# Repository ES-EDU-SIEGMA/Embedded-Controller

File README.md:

# Drink Mixing Machine Controller

This repository provides the source code for the RP2040 based stepper driver controller.
Further documentation of the hardware can be found in
the [main](https://git.uni-due.de/embedded-systems/student-projects/ss23-drink-mixing-machine/main) repository.

**The main branch of this repository can be considered stable and should be working at all time.**

## Local DEV Environment

### Toolchain

Required tools for the toolchain are:

- gcc (C-Compiler)
- arm-none-eabi-gcc (ARM C-Compiler)
- CMake (Build Script Generator)
- Ninja/Make (Build Tool)

### Build with CMake

#### Genrate Build Scripts

The build scripts can be generated by executing CMake in your Terminal as follows:

```bash
cmake -B build/<profile> -DUNIT_TEST:BOOL=<ON/OFF>  -DDEBUG:BOOL=<ON/OFF> -DCMAKE_BUILD_TYPE=<Debug/MinSizeRel>
```

The profile is one of three:

- _debug_
- _release_
- _unittest_

The `UNIT_TEST` option should be _ON_ for the unit-test profile and otherwise _OFF_.

The `DEBUG` option should be _OFF_ for the release profile and otherwise _ON_ to enable enhanced debug output.

The `CMAKE_BUILD_TYPE` option should be set to _MinSizeRel_ for the final targets to flash the machine for operations,
because otherwise the application provides too much output, that disturb the Python-based control application.

#### Build Targets

The targets to flash the Tiny2040 can be built by running

```bash
cmake --build build/<profile> -j4
```

The profile is one of three:

- _debug_
- _release_
- _unit-test_

## Contribution Guidelines

The source code should be formatted according to the style specified in the [.clang-format](.clang-format) file.

There are no direct commits to the main branch allowed.
If you want to contribute source-code, feel free to open a merge request with your desired changes.

### Folder Structure

The source code for the target device can be found under [src](src).
The [integration](test/integration) folder provides you with the integration tests which also double as an example for
the usage of the provided libraries.
The unit-tests aim to be executed on the local machine/server and are implemented under [unit](test/unit).

## Troubleshooting

### Serial Communication (Debugging)

The application detects the end of a send command by searching for _EOL_ (0x0A) or `\n`.
This character is not on the standard keyboard!
In minicom, for example, it can be sent with `CTRL+J`.

### Stepper Driver not working

Try with Arduino mega with example code from the TMC2209 library each stepper driver.
If the stepper driver is still not working, test after taking each of those steps:

- Check each connection
- Make sure TX and RX are correctly wired
- Use multiple different stepper drivers
- Use different USB cable to connect your computer
- Replace resistors
- Try with a different computer

If it works with the Arduino, the connections are all correct.
Try again with the pico.
If it does not work:

- Replace the pico
- Use different cable to connect your computer
- Use a different computer

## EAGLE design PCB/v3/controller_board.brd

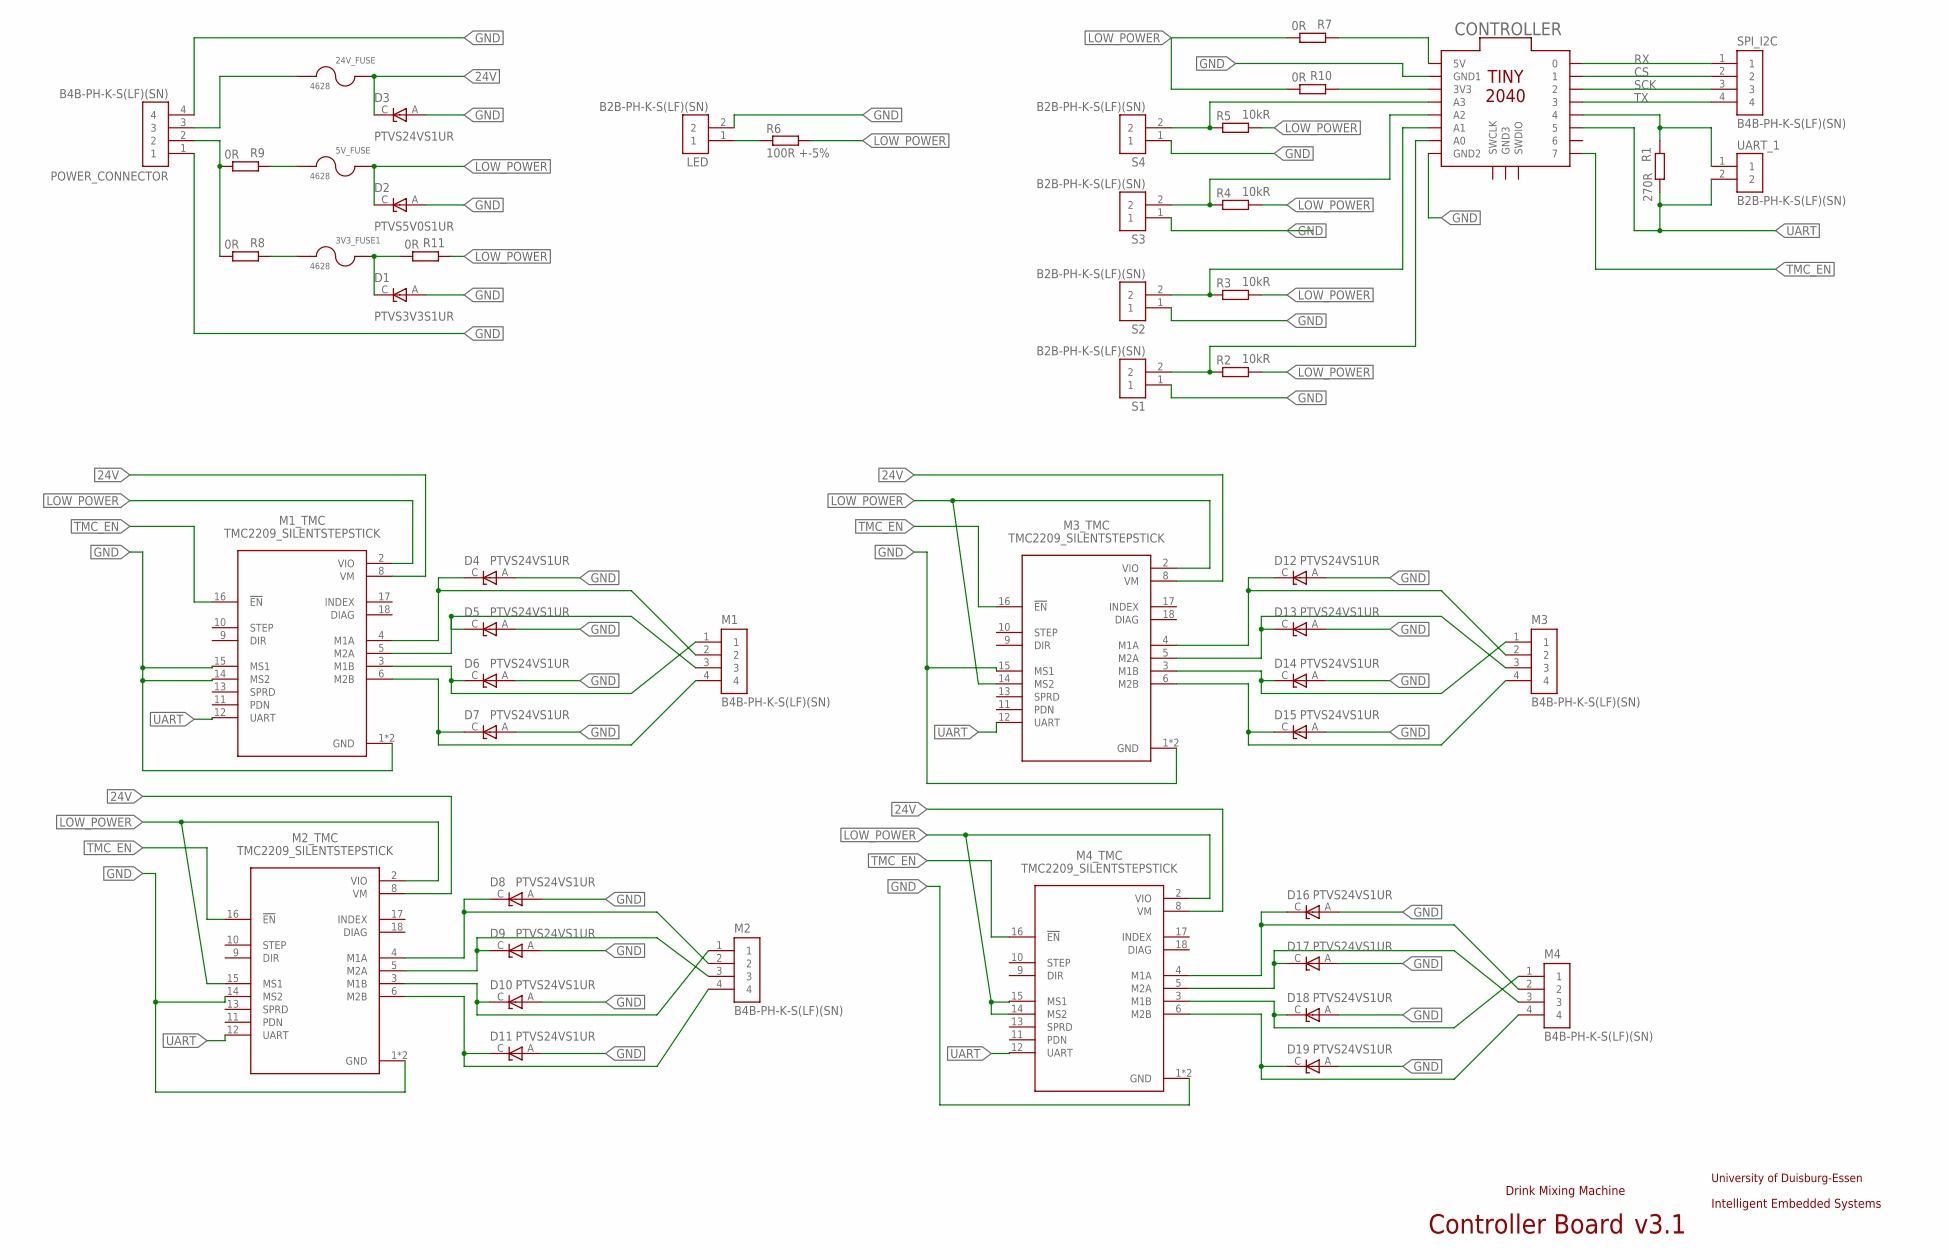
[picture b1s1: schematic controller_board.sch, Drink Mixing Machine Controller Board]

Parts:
3V3_FUSE1, 5V_FUSE, 24V_FUSE: 4628; FUSE_4628
CONTROLLER: TINY2040_HEADER
D1: PTVS3V3S1UR; TVS_PTVS3V3S1UR
D2: PTVS5V0S1UR; TVS_PTVS5V0S1UR
D3, D4, D5, D6, D7, D8, D9, D10, D11, D12, D13, D14, D15, D16, D17, D18, D19: PTVS24VS1UR; TVS_PTVS24VS1UR
LED: B2B-PH-K-S(LF)(SN); JST_B2B-PH-K-S(LF)(SN)
M1, M2, M3, M4: B4B-PH-K-S(LF)(SN); JST_B4B-PH-K-S(LF)(SN)
M1_TMC, M2_TMC, M3_TMC, M4_TMC: TMC2209_SILENTSTEPSTICK; MODULE_TMC2209_SILENTSTEPSTICK
POWER_CONNECTOR: B4B-PH-K-S(LF)(SN); JST_B4B-PH-K-S(LF)(SN)
R1: 270R; R0805
R2, R3, R4, R5: 10kR; R0805
R6: 100R +-5%; R0805
R7, R8, R9, R10, R11: 0R; R0805
S1, S2, S3, S4: B2B-PH-K-S(LF)(SN); JST_B2B-PH-K-S(LF)(SN)
SPI_I2C: B4B-PH-K-S(LF)(SN); JST_B4B-PH-K-S(LF)(SN)
UART_1: B2B-PH-K-S(LF)(SN); JST_B2B-PH-K-S(LF)(SN)

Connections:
3V3: 3V3_FUSE1.2, D1.C, R11.2
24V: 24V_FUSE.2, D3.C, M1_TMC.8 (VM), M2_TMC.8 (VM), M3_TMC.8 (VM), M4_TMC.8 (VM)
A0: CONTROLLER.A0, R2.1, S1.2
A1: CONTROLLER.A1, R3.1, S2.2
A2: CONTROLLER.A2, R4.1, S3.2
CS: CONTROLLER.1, SPI_I2C.2
GND: CONTROLLER.GND1, CONTROLLER.GND2, D1.A, D2.A, D3.A, D4.A, D5.A, D6.A, D7.A, D8.A, D9.A, D10.A, D11.A, D12.A, D13.A, D14.A, D15.A, D16.A, D17.A, D18.A, D19.A, LED.2, M1_TMC.1 (GND), M1_TMC.7 (GND), M1_TMC.14 (MS2), M1_TMC.15 (MS1), M2_TMC.1 (GND), M2_TMC.7 (GND), M2_TMC.14 (MS2), M3_TMC.1 (GND), M3_TMC.7 (GND), M3_TMC.15 (MS1), M4_TMC.1 (GND), M4_TMC.7 (GND), POWER_CONNECTOR.1, POWER_CONNECTOR.4, S1.1, S2.1, S3.1, S4.1
LOW_POWER: 5V_FUSE.2, D2.C, M1_TMC.2 (VIO), M2_TMC.2 (VIO), M2_TMC.15 (MS1), M3_TMC.2 (VIO), M3_TMC.14 (MS2), M4_TMC.2 (VIO), M4_TMC.14 (MS2), M4_TMC.15 (MS1), R2.2, R3.2, R4.2, R5.2, R6.2, R7.2, R10.2, R11.1
unnamed: POWER_CONNECTOR.2, R8.2, R9.2
unnamed: D4.C, M1.2, M1_TMC.4 (M1A)
unnamed: 5V_FUSE.1, R9.1
unnamed: D6.C, M1.1, M1_TMC.3 (M1B)
unnamed: D8.C, M2.2, M2_TMC.4 (M1A)
unnamed: D11.C, M2.4, M2_TMC.6 (M2B)
unnamed: D9.C, M2.3, M2_TMC.5 (M2A)
unnamed: D10.C, M2.1, M2_TMC.3 (M1B)
unnamed: D12.C, M3.2, M3_TMC.4 (M1A)
unnamed: D15.C, M3.4, M3_TMC.6 (M2B)
unnamed: D13.C, M3.3, M3_TMC.5 (M2A)
unnamed: D14.C, M3.1, M3_TMC.3 (M1B)
unnamed: D16.C, M4.2, M4_TMC.4 (M1A)
unnamed: D19.C, M4.4, M4_TMC.6 (M2B)
unnamed: D17.C, M4.3, M4_TMC.5 (M2A)
unnamed: D18.C, M4.1, M4_TMC.3 (M1B)
unnamed: LED.1, R6.1
unnamed: CONTROLLER.5V, R7.1
unnamed: D7.C, M1.4, M1_TMC.6 (M2B)
unnamed: CONTROLLER.4, R1.1, UART_1.1
unnamed: 3V3_FUSE1.1, R8.1
unnamed: 24V_FUSE.1, POWER_CONNECTOR.3
unnamed: CONTROLLER.3V3, R10.1
unnamed: CONTROLLER.A3, R5.1, S4.2
unnamed: D5.C, M1.3, M1_TMC.5 (M2A)
RX: CONTROLLER.0, SPI_I2C.1
SCK: CONTROLLER.2, SPI_I2C.3
TMC_EN: CONTROLLER.7, M1_TMC.16 (!EN), M2_TMC.16 (!EN), M3_TMC.16 (!EN), M4_TMC.16 (!EN)
TX: CONTROLLER.3, SPI_I2C.4
UART: CONTROLLER.5, M1_TMC.12 (UART), M2_TMC.12 (UART), M3_TMC.12 (UART), M4_TMC.12 (UART), R1.2, UART_1.2

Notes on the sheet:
Intelligent Embedded Systems
University of Duisburg-Essen
Drink Mixing Machine
Controller Board

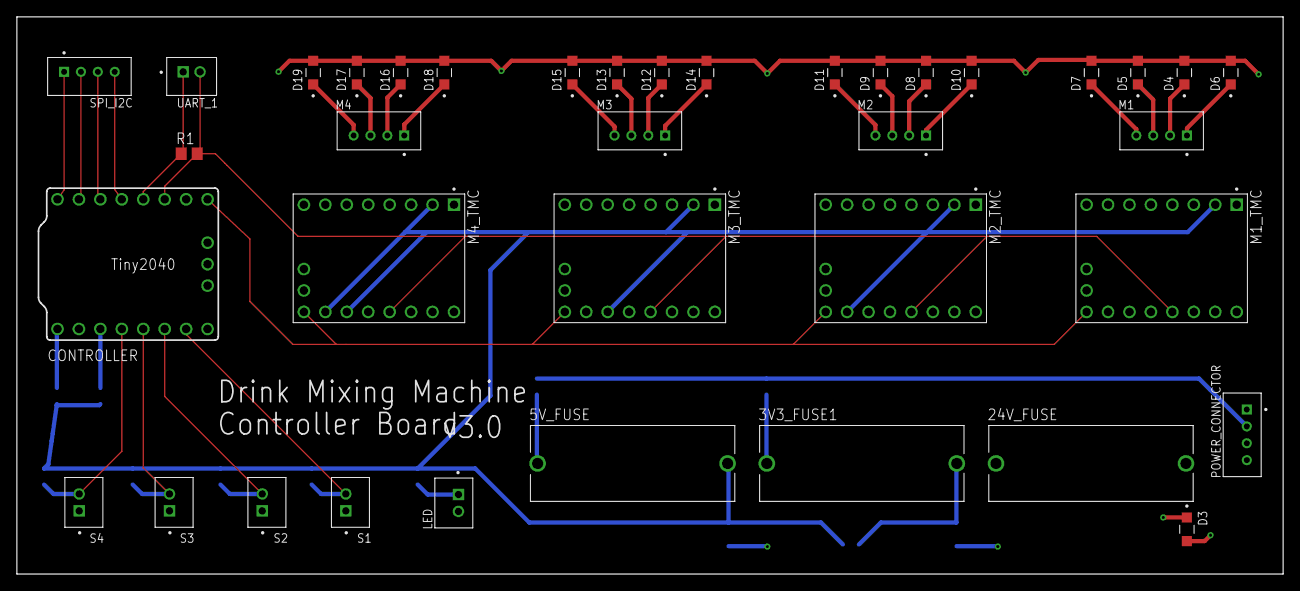
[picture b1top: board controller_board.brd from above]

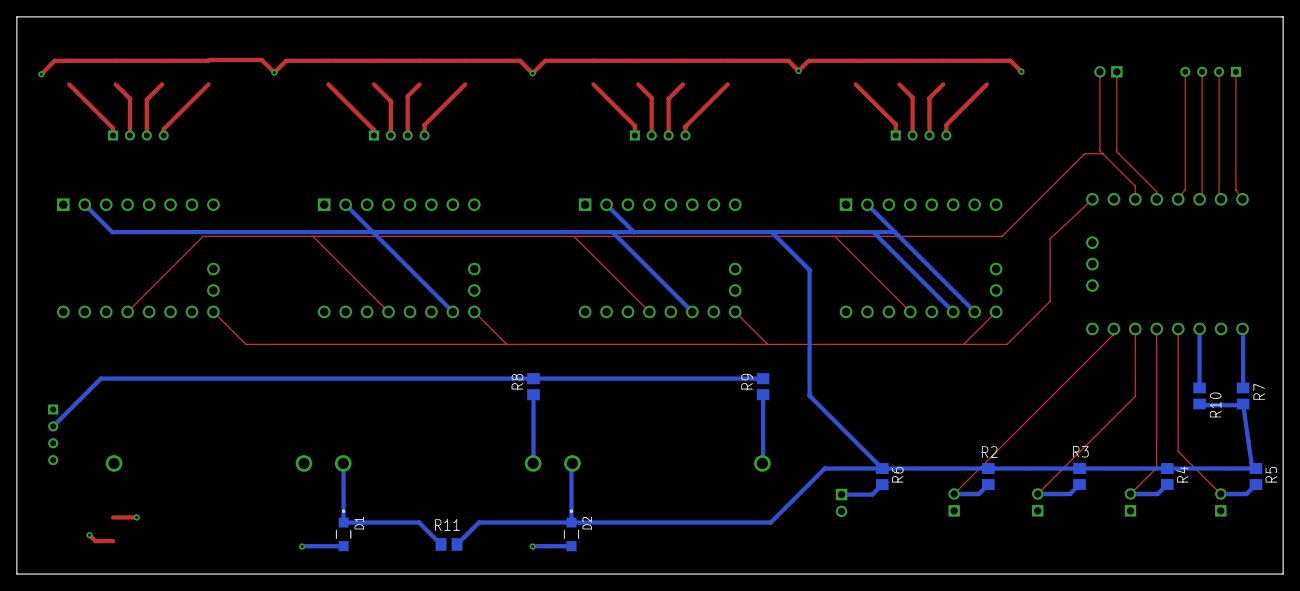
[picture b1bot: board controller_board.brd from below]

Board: 4 copper layers, 150.0 x 66.0 mm, 50 parts (12 on the bottom side), 38 nets.

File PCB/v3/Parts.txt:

Partlist

Exported from controller_board.sch at 06.02.24 19:13

EAGLE Version 9.6.2 Copyright (c) 1988-2020 Autodesk, Inc.

Assembly variant: 

Part            Value                   Device                  Package                        Library                 Sheet

3V3_FUSE1       4628                    4628                    FUSE_4628                      4628                    1
5V_FUSE         4628                    4628                    FUSE_4628                      4628                    1
24V_FUSE        4628                    4628                    FUSE_4628                      4628                    1
CONTROLLER      TINY2040_HEADER         TINY2040_HEADER         TINY2040_HEADER                tiny2040_headerd        1
D1              PTVS3V3S1UR             PTVS3V3S1UR             TVS_PTVS3V3S1UR                PTVS3V3S1UR             1
D2              PTVS5V0S1UR             PTVS5V0S1UR             TVS_PTVS5V0S1UR                PTVS5V0S1UR             1
D3              PTVS24VS1UR             PTVS24VS1UR             TVS_PTVS24VS1UR                PTVS24VS1UR             1
D4              PTVS24VS1UR             PTVS24VS1UR             TVS_PTVS24VS1UR                PTVS24VS1UR             1
D5              PTVS24VS1UR             PTVS24VS1UR             TVS_PTVS24VS1UR                PTVS24VS1UR             1
D6              PTVS24VS1UR             PTVS24VS1UR             TVS_PTVS24VS1UR                PTVS24VS1UR             1
D7              PTVS24VS1UR             PTVS24VS1UR             TVS_PTVS24VS1UR                PTVS24VS1UR             1
D8              PTVS24VS1UR             PTVS24VS1UR             TVS_PTVS24VS1UR                PTVS24VS1UR             1
D9              PTVS24VS1UR             PTVS24VS1UR             TVS_PTVS24VS1UR                PTVS24VS1UR             1
D10             PTVS24VS1UR             PTVS24VS1UR             TVS_PTVS24VS1UR                PTVS24VS1UR             1
D11             PTVS24VS1UR             PTVS24VS1UR             TVS_PTVS24VS1UR                PTVS24VS1UR             1
D12             PTVS24VS1UR             PTVS24VS1UR             TVS_PTVS24VS1UR                PTVS24VS1UR             1
D13             PTVS24VS1UR             PTVS24VS1UR             TVS_PTVS24VS1UR                PTVS24VS1UR             1
D14             PTVS24VS1UR             PTVS24VS1UR             TVS_PTVS24VS1UR                PTVS24VS1UR             1
D15             PTVS24VS1UR             PTVS24VS1UR             TVS_PTVS24VS1UR                PTVS24VS1UR             1
D16             PTVS24VS1UR             PTVS24VS1UR             TVS_PTVS24VS1UR                PTVS24VS1UR             1
D17             PTVS24VS1UR             PTVS24VS1UR             TVS_PTVS24VS1UR                PTVS24VS1UR             1
D18             PTVS24VS1UR             PTVS24VS1UR             TVS_PTVS24VS1UR                PTVS24VS1UR             1
D19             PTVS24VS1UR             PTVS24VS1UR             TVS_PTVS24VS1UR                PTVS24VS1UR             1
LED             B2B-PH-K-S(LF)(SN)      B2B-PH-K-S(LF)(SN)      JST_B2B-PH-K-S(LF)(SN)         B2B-PH-K-S_LF__SN_      1
M1              B4B-PH-K-S(LF)(SN)      B4B-PH-K-S(LF)(SN)      JST_B4B-PH-K-S(LF)(SN)         B4B-PH-K-S_LF__SN_      1
M1_TMC          TMC2209_SILENTSTEPSTICK TMC2209_SILENTSTEPSTICK MODULE_TMC2209_SILENTSTEPSTICK TMC2209_SILENTSTEPSTICK 1
M2              B4B-PH-K-S(LF)(SN)      B4B-PH-K-S(LF)(SN)      JST_B4B-PH-K-S(LF)(SN)         B4B-PH-K-S_LF__SN_      1
M2_TMC          TMC2209_SILENTSTEPSTICK TMC2209_SILENTSTEPSTICK MODULE_TMC2209_SILENTSTEPSTICK TMC2209_SILENTSTEPSTICK 1
M3              B4B-PH-K-S(LF)(SN)      B4B-PH-K-S(LF)(SN)      JST_B4B-PH-K-S(LF)(SN)         B4B-PH-K-S_LF__SN_      1
M3_TMC          TMC2209_SILENTSTEPSTICK TMC2209_SILENTSTEPSTICK MODULE_TMC2209_SILENTSTEPSTICK TMC2209_SILENTSTEPSTICK 1
M4              B4B-PH-K-S(LF)(SN)      B4B-PH-K-S(LF)(SN)      JST_B4B-PH-K-S(LF)(SN)         B4B-PH-K-S_LF__SN_      1
M4_TMC          TMC2209_SILENTSTEPSTICK TMC2209_SILENTSTEPSTICK MODULE_TMC2209_SILENTSTEPSTICK TMC2209_SILENTSTEPSTICK 1
POWER_CONNECTOR B4B-PH-K-S(LF)(SN)      B4B-PH-K-S(LF)(SN)      JST_B4B-PH-K-S(LF)(SN)         B4B-PH-K-S_LF__SN_      1
R1              270R                    R-EU_R0805              R0805                          rcl                     1
R2              10kR                    R-EU_R0805              R0805                          rcl                     1
R3              10kR                    R-EU_R0805              R0805                          rcl                     1
R4              10kR                    R-EU_R0805              R0805                          rcl                     1
R5              10kR                    R-EU_R0805              R0805                          rcl                     1
R6              100R +-5%               R-EU_R0805              R0805                          rcl                     1
R7              0R                      R-EU_R0805              R0805                          rcl                     1
R8              0R                      R-EU_R0805              R0805                          rcl                     1
R9              0R                      R-EU_R0805              R0805                          rcl                     1
R10             0R                      R-EU_R0805              R0805                          rcl                     1
R11             0R                      R-EU_R0805              R0805                          rcl                     1
S1              B2B-PH-K-S(LF)(SN)      B2B-PH-K-S(LF)(SN)      JST_B2B-PH-K-S(LF)(SN)         B2B-PH-K-S_LF__SN_      1
S2              B2B-PH-K-S(LF)(SN)      B2B-PH-K-S(LF)(SN)      JST_B2B-PH-K-S(LF)(SN)         B2B-PH-K-S_LF__SN_      1
S3              B2B-PH-K-S(LF)(SN)      B2B-PH-K-S(LF)(SN)      JST_B2B-PH-K-S(LF)(SN)         B2B-PH-K-S_LF__SN_      1
S4              B2B-PH-K-S(LF)(SN)      B2B-PH-K-S(LF)(SN)      JST_B2B-PH-K-S(LF)(SN)         B2B-PH-K-S_LF__SN_      1
SPI_I2C         B4B-PH-K-S(LF)(SN)      B4B-PH-K-S(LF)(SN)      JST_B4B-PH-K-S(LF)(SN)         B4B-PH-K-S_LF__SN_      1
UART_1          B2B-PH-K-S(LF)(SN)      B2B-PH-K-S(LF)(SN)      JST_B2B-PH-K-S(LF)(SN)         B2B-PH-K-S_LF__SN_      1

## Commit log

2023-04-19 chore(ide): remove IDE settings
2023-04-19 fix build: fixed build files / includes
2023-04-19 refactor(integration-test): apply format options
2023-04-19 refactor(unit-test): apply format
2023-04-19 docs(readme): update
2023-04-21 build(target):
    Update CMake files for target Tiny2040
2023-04-21 refactor(main):
    refactored main file for improved readability
2023-04-21 refactor(dispenser):
    refacor dispenser library for improved readability
2023-04-21 refactor(dispenser):
    refactor dispenser library for improved readability
2023-04-21 refactor(limitSwitch):
    refactor limitSwitch library for improved readability
2023-04-21 refactor(motor):
    refactor motor library for improved readability
2023-04-22 refactor(rondell):
    refactor rondell library for improved readability
2023-04-22 refactor(serialUart):
    refactor serial UART library for improved readability
2023-04-22 refactor(tmc2209):
    refactor tmc2209 library for improved readability
2023-04-22 refactor(integration-test):
    applied refactoring
2023-04-22 fix(integration-test): fix dispenser
2023-04-24 Correct mistake
2023-04-26 chore(common): add PRINT_COMMAND makro
    Add special makro for commands required for the implementation and communication with the Pi
2023-04-26 style(debug-print): apply print makros
2023-04-26 style(rondell): move static functions to internal header
2023-04-26 test(dispenser): added documentation for integration-test
2023-04-27 fix(main)(fix dispensing liquids):
    Functions was wrong due to flase refactoring
2023-04-28 fix(dispenser): change `elifdef` to `if defined(...)``
2023-04-28 fix(dispenser): replaced PRINT with PRINT_DEBUG
2023-04-28 fix(rondell): renamed RONDELL_POSITION
2023-05-09 perf(main): add watchdog timer
    add watchdog time of 15s
    improved readability by extracting code into functions
    declared function prototypes for internal functions
2023-05-09 fix(main): fix processMessage
2023-05-12 chore(git): update ignore
2023-05-12 style(main): minor changes on main loop
2023-05-14 build(target): split into three targets
    removed one main.c target and split up into left/right/rondell
    BREAKING CHANGE: Split hardware target into differnt build targets
2023-05-14 refactor(dispenser): remove LEFT/RIGHT/RONDELL flag from dispenser lib
2023-05-14 refactor(limitSwitch): update dependencies
2023-05-14 refactor(motor): update dependencies
2023-05-15 build(target): fully removed LEFT/RIGHT/RONDELL flag
2023-05-15 test(integration-test): refacor tests to compile after build script changes
2023-05-17 perf(helper): introduced helper to
    BREAKING CHANGE: description new awaits pointer to store data
2023-05-23 fix(watchdog): fix implementation so that watchdog is working correctly
2023-06-04 test(dispenser rigth side): Changed speed to 150000 and adjusted Steps. Added missing breaks.
2023-06-11 feat(speed of dispenser): New function to calculate the moving up time of the dispenser
2023-06-13 fix(rondell): add second watchdog timer reset
2023-06-18 feat(speed of dispenser): Apply Davids Code suggestions
2023-06-19 feat(speed of dispenser): Making Speed Function static
2023-06-20 Apply suggestions from code review
2023-06-27 fix(Dispenser): UpTime in Milliseconds
2023-06-27 feat(ramp for Dispenser): Two speeds are possible for the up-driving, slow and fast
2023-06-29 fix(Dispenser-Speed): Calculation of stepsPerSecond
2023-07-04 feat(dispenser): Parameter changes for ramp for Dispenser
2023-07-05 chore(git):
2023-07-05 build(pico-sdk): update pico-sdk to latest release
2023-07-05 test(dispenser): fix integration for dispeneser
2023-07-05 fix(rondell): reduce motor speed of rondell
    required due to the fact,
    that the sensor is not fast enough otherwise
2023-07-05 docs(readme): add 'how to use CMake' part
2023-07-06 feat(dispenser): If only one speed is required, set stepsFastSpeed = 0
2023-07-06 refactor(dispenser): Deleted unused variables
2023-07-07 refactor(ramp): Some Code changes and comments for a better understanding
2023-07-07 feat(torqueRecognition): Added functions to tmc2209.c
2023-07-07 feat(torqueRecognition): Torque Measuring does work
2023-07-09 feat(Dispenser): top State Detection
2023-07-10 fix(Speed of Dispenser): Adjust speed of Dispenser
2023-07-25 feat(Dispenser): Better top State Detection and downstate only reached by limitSwitch
2023-10-24 chore(PCB): moved old files to subfolder
2023-10-24 doc(PCB): add new board schematics (AUTODESK EAGLE)
2023-11-05 chore(pcb): improve schematics
2023-11-06 feat(pcb): add ESD protection
2023-11-07 refactor(Dispenser): Deleted Functions for time calculation for the up driving
2023-11-07 feat(pcb): add proper PCB layout
2023-11-07 Measuring torque - Logic of processMessage, time consumption optimized
2023-11-07 Measuring torque - Logic of processMessage, time consumption optimized. Removed testing code
2023-11-07 refactor(Dispenser): Deleted Function for direction search
2023-11-07 refactor(Dispenser): When limit switch is closed in initialization, motor does not move
2023-11-07 refactor(Dispenser): Deleted find direction function
2023-11-08 feat(pcb): add wires
2023-11-13 feat(pcb): add 3V3 circuit
2023-11-14 feat(pcb): replace ESD protection with TVS-Diode
2023-11-16 #41 perf(torque) measure torque's value more frequently.
2023-11-16 feat(pcb): add TMC enable pin
2023-11-16 chore(pcb): rename folder to correct version
2023-11-17 fix(pcb): fix tiny2040 library
2023-11-17 chore(pcb): add libraries
2023-12-01 refactoring libraries
2023-12-12 docs(pcb): added gerber files for JCLPCB 4-layer
    Added Eagle generated gerber files based on jclpcb provided CAM file
    -> added too!
2023-12-12 feat(Dispenser): The lever from all dispensers drives in the initialization directly under the dispenser and stops
2023-12-14 feat(Dispenser): The lever from all dispensers, after emptying has taken place, drives under the dispenser and stops
2023-12-14 fix(Controller): The new timing behavior for the right dipsensor and the rondel has been updated like it is in the left dispenser.
2023-12-15 feat(Dispenser): Code does work with one or two dispenser triggered, but not with 3 or more triggered
2023-12-16 refactor(dispenser): new implementation of time to hold at top
2023-12-17 feat(Dispenser): New Variables for Dispenser
2023-12-17 test(unit test): fix and improve the coverage of unit test
2023-12-17 feat(Dispenser): Now the code should work also with 3 and more dispenser in parallel. There was a while Loop in the downState function which caused the problem.
2023-12-17 feat(Dispenser): Higher speed implemented for the up-driving of the lever to the start of the Dispenser.
2023-12-18 fix(integrationTest_dispenser.c): can be build for now.
2023-12-18 test(unit test hardwareHelper): test more hardwareHelper functions.
2023-12-18 fix(unit test dispenser): fix the parameter uart used by dispenserCreate
2023-12-18 test(unit test hardwareHelper): test more functions in hardwareHelper.c
2023-12-19 feat(Dispenser): Not it works and is tested
2023-12-19 fix(unit test): fixed two multi-definition errors
2023-12-19 fix(unit test): naming, undeclared errors
2023-12-22 docs(pcb). add part list with order links
2023-12-24 refactoring remaining libraries
2023-12-30 feat(Dispenser): Not finished
2023-12-31 feat(Dispenser): Not finished, Unit Test working
2023-12-31 refactor(UnitTest): Unit Test working
2023-12-31 refactor: Removed SearchTimeout
2023-12-31 Refactoring
2024-01-01 feat(dispenser): Added torque detection in resetDispenserPosition and downstate
2024-01-01 feat(tmc2209): Added function for Motor-Position
2024-01-07 feat(lever-Stop): Function for initialization ready
2024-01-07 feat(lever-Stop): Function for phase after init ready for test
2024-01-08 bug(main): function to other position
2024-01-08 test(unit test dispenser): test the cycle of a working dispenser.
2024-01-09 test(unit test dispenser): remove unnecessary dummy code and file.
2024-01-09 test(unit-tests): remove header files from add_executable
2024-01-14 bug(main-Code): Moved function to other position
2024-01-15 feat(Lever-Stop): Function optimization
2024-01-15 feat(Lever-Stop): Removed todos
2024-01-15 feat(Lever-Stop): The Lever drives a few steps down after stopping, so that no water comes out.
2024-01-23 perf(dispenser): change torque to dispenser->torque, reduce the sleep time in TMC2209_read, measure torque more frequently.
2024-02-02 refactor(Motor-GPIO): With the new PCB only one Enable/Disable Pin is available for all Motors
2024-02-02 refactor(Motor-Enable): Some more refactoring for the enable pin
2024-02-03 fix(pico-sdk): set referenced versio to last release!!
2024-02-03 test(integration): update tests
2024-02-05 fix(limitswitch) test(adc): fix limitswitch/adc gpio asscoiations
2024-02-06 style(motor): apply formatting
2024-02-06 test(motor): fix TMC initialization
2024-02-06 fix(schmatic): update UART resistor value
2024-02-13 fix(unit-test): rewrite the dummy torque value, fixed failing unit-test_dispenser.
2024-02-13 fix(unit-test): remove TODOs.
2024-02-20 fix controller by moving motorsenablepin before dispenser
2024-02-20 fix wrong
2024-02-20 fix controller by moving the MotorsEnablePin before dispenser init
2024-02-20 move motor check out of do while
2024-02-20 move motor check out of do while--right_controller
2024-02-27 perf(dispenser): use new common counter to let dispenser make a proper countdown.
2024-02-27 fix(dispenser): fix multi-definition.
2024-02-27 perf(dispenser): countdown method to realize more accurate halt time.
2024-02-27 perf(dispenser): change time to wait TMC switch off output to 21us and add sleep 1ms in topState to approximate halt time.
2024-02-27 perf(dispenser): remove test code. Test with command 10000 and actual halt time is roughly about 10s.
2024-02-28 fix(motor): build(cmake): pass motor speed via CMake target
2024-02-28 refactor(controller): move endless loop to noreturn function
2024-02-29 fix(dispenser): fix motor init
2024-02-29 test(dispenser): add velocity
2024-02-29 fix(dispenser): add more accurate halt time back and remove redundant TMC_moveAtVelocity call.
2024-02-29 add dispenserErrorStateCheck before doWhile in left/right controller
2024-03-01 fix datatype of haltime and add some comments.
2024-03-01 remove commented out code in motor.
2024-03-01 Use uint32_t for haltTime again and check underflow of haltTime countdown.
2024-06-06 ci(cmake): replace git submodules with cmake fetch
2024-06-06 fix(com-protocol): extraxt communication protocol
2024-06-06 fix(all): controller
2024-06-06 feat(controller): move send ID to main loop
2024-06-09 fix(controller): command for string equal check
2024-06-10 fix(dispenser): enable disabling contact state for rondell
2024-06-12 fix(controller): fixes for demo
